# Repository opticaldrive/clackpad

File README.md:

# clackpad

This is a 2x4 macropad with neopixel underlighting! It's supposed to help make me more productive(WIP) on my computer\
Not pictured is a gesture sensor, which is present on the physical pcb(but the case doesn't have a hole for it sob) \
| Item Name | Description | Quantity | Cost |
|-----------|-------------|----------|------|
| PCB | Main Macropad PCB | 5 | ~9USD |
| Seeed Studio Xiao RP2040 | Main MCU | 1 | N/A Hackpad Provided |
| CherryMX Switches | Keyswitches, the buttons on the macropad | 8 | N/A Hackpad Provided |
| Diodes | Diodes for matrix to prevent ghosting | 8 | N/A Hackpad Provided |
| SK6812 MINI-E  | backlighting? flashing? neopixels! | 8 | N/A Hackpad Provided |

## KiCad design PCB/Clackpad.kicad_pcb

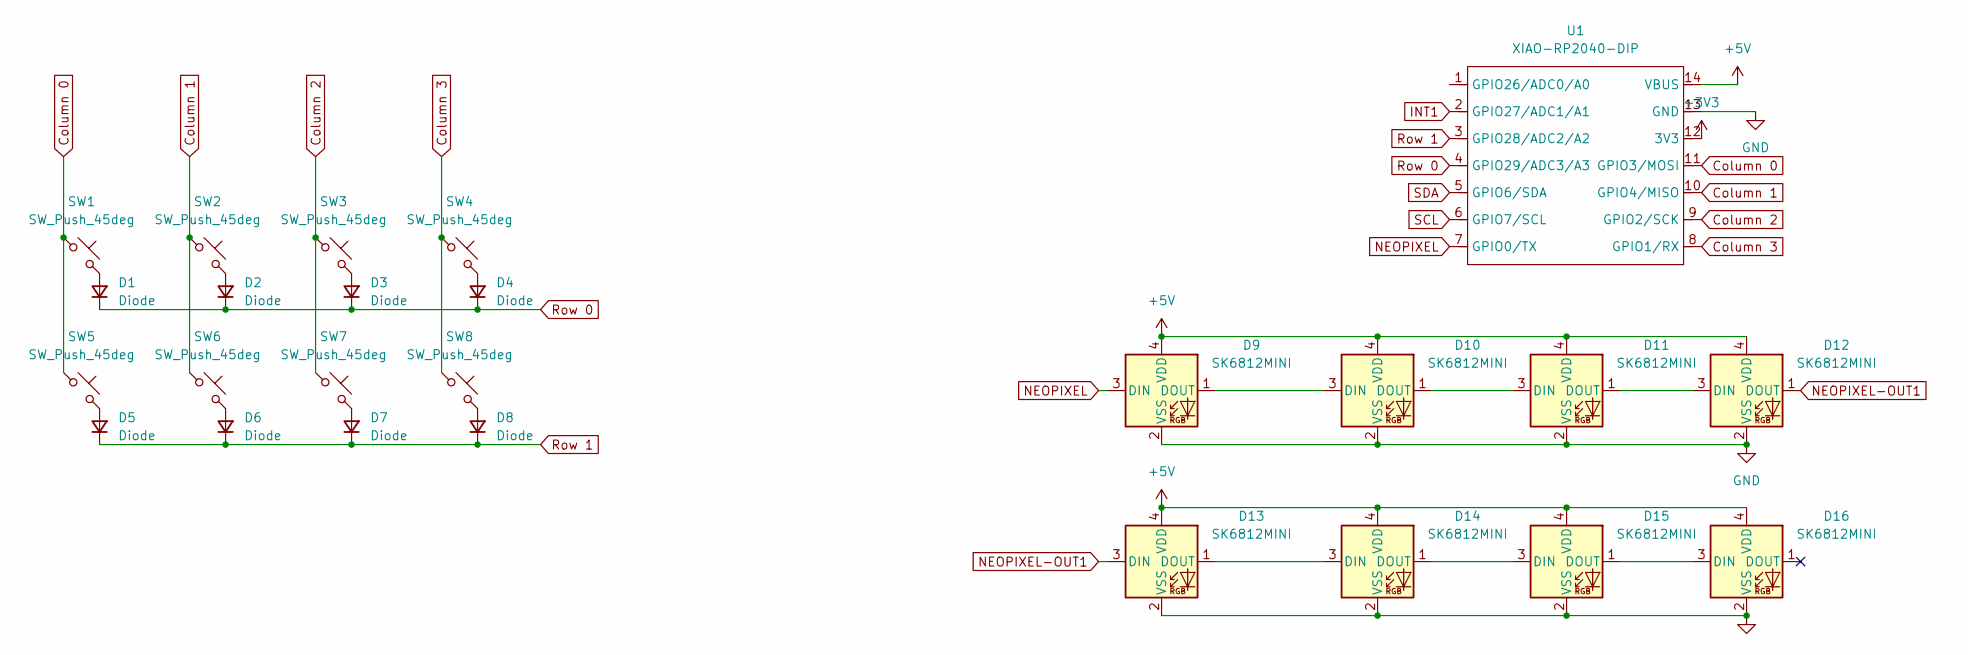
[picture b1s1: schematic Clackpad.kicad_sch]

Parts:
D1, D2, D3, D4, D5, D6, D7, D8: Diode; D_DO-35_SOD27_P7.62mm_Horizontal
D9, D10, D11, D12, D13, D14, D15, D16: SK6812MINI; SK6812-MINI-E
SW1, SW2, SW3, SW4, SW5, SW6, SW7, SW8: SW_Push_45deg; SW_Cherry_MX_1.00u_PCB
U1: XIAO-RP2040-DIP

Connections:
+3V3: U1.12 (3V3)
+5V: D9.4 (VDD), D10.4 (VDD), D11.4 (VDD), D12.4 (VDD), D13.4 (VDD), D14.4 (VDD), D15.4 (VDD), D16.4 (VDD), U1.14 (VBUS)
Column 0: SW1.1, SW5.1, U1.11 (GPIO3/MOSI)
Column 1: SW2.1, SW6.1, U1.10 (GPIO4/MISO)
Column 2: SW3.1, SW7.1, U1.9 (GPIO2/SCK)
Column 3: SW4.1, SW8.1, U1.8 (GPIO1/RX)
GND: D9.2 (VSS), D10.2 (VSS), D11.2 (VSS), D12.2 (VSS), D13.2 (VSS), D14.2 (VSS), D15.2 (VSS), D16.2 (VSS), U1.13 (GND)
INT1: U1.2 (GPIO27/ADC1/A1)
NEOPIXEL: D9.3 (DIN), U1.7 (GPIO0/TX)
NEOPIXEL-OUT1: D12.1 (DOUT), D13.3 (DIN)
unnamed: D1.2 (A), SW1.2
unnamed: D2.2 (A), SW2.2
unnamed: D3.2 (A), SW3.2
unnamed: D4.2 (A), SW4.2
unnamed: D5.2 (A), SW5.2
unnamed: D6.2 (A), SW6.2
unnamed: D7.2 (A), SW7.2
unnamed: D8.2 (A), SW8.2
unnamed: D9.1 (DOUT), D10.3 (DIN)
unnamed: D10.1 (DOUT), D11.3 (DIN)
unnamed: D11.1 (DOUT), D12.3 (DIN)
unnamed: D13.1 (DOUT), D14.3 (DIN)
unnamed: D14.1 (DOUT), D15.3 (DIN)
unnamed: D15.1 (DOUT), D16.3 (DIN)
Row 0: D1.1 (K), D2.1 (K), D3.1 (K), D4.1 (K), U1.4 (GPIO29/ADC3/A3)
Row 1: D5.1 (K), D6.1 (K), D7.1 (K), D8.1 (K), U1.3 (GPIO28/ADC2/A2)
SCL: U1.6 (GPIO7/SCL)
SDA: U1.5 (GPIO6/SDA)

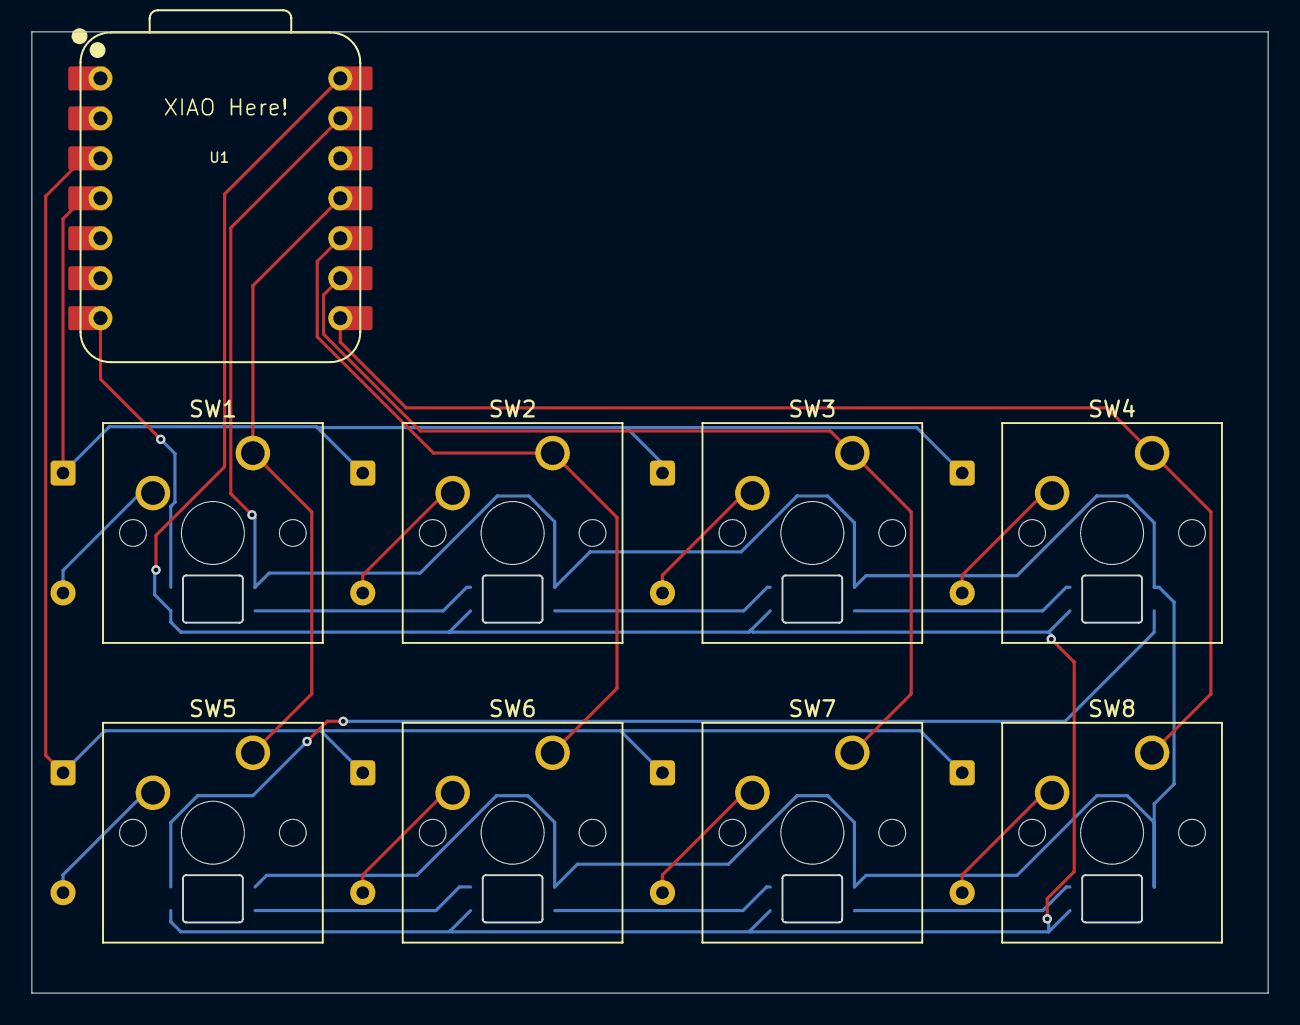
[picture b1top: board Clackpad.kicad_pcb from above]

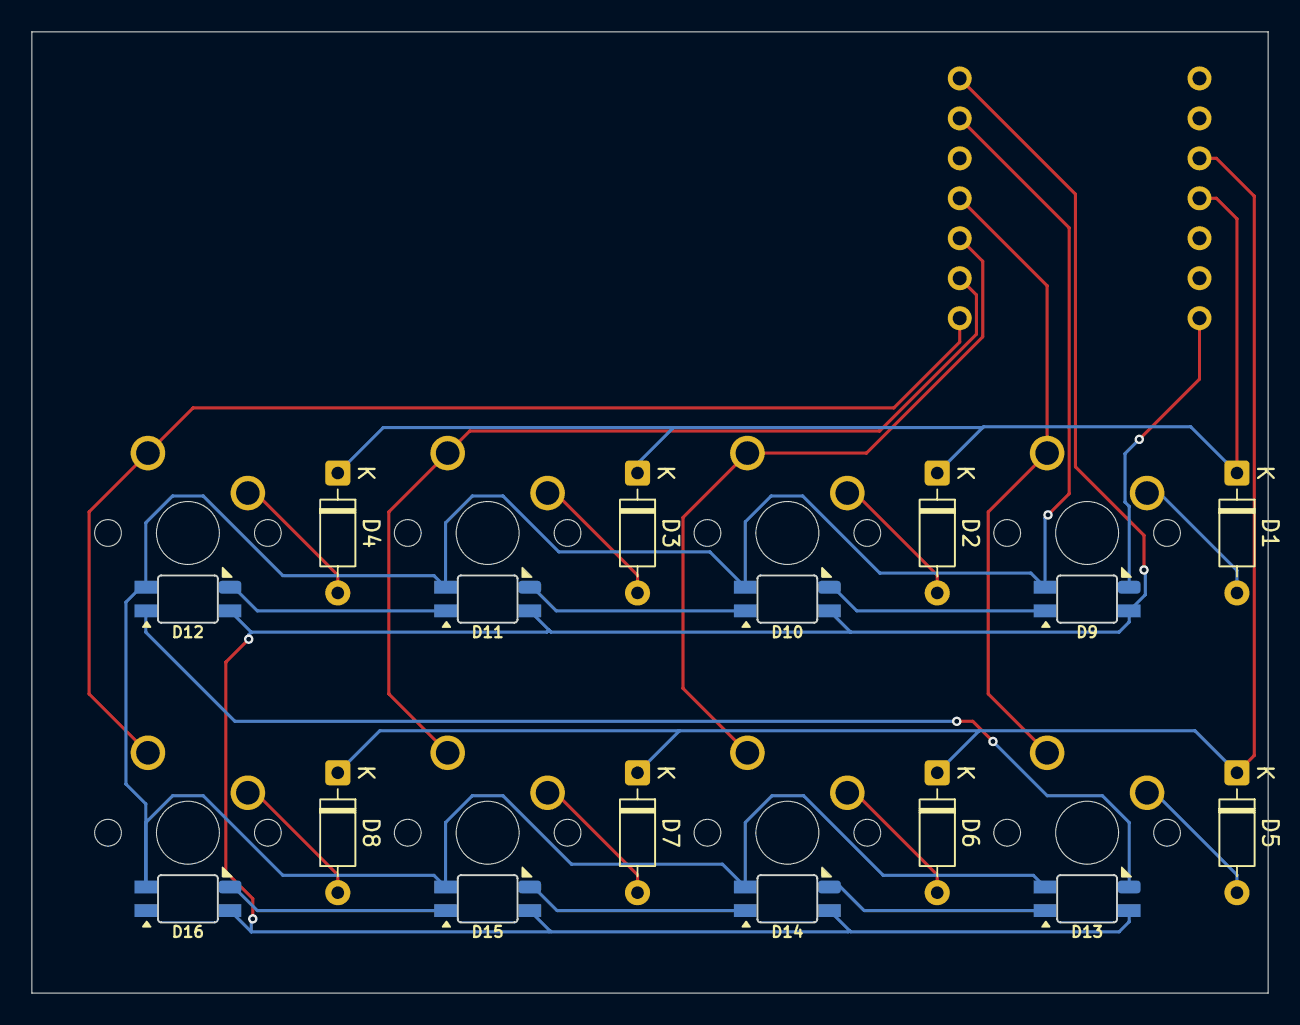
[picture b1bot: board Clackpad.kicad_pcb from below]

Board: 2 copper layers, 78.5 x 61.0 mm, 25 parts (16 on the bottom side), 24 nets.

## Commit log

2025-07-10 Adding some prod files - no firmware
2025-07-10 readme or not
2025-07-10 firmware 1
2025-07-10 duplicates yay
2025-07-10 hope this works
2025-07-10 commit go
2025-07-10 [ImgBot] Optimize images
    *Total -- 619.48kb -> 431.71kb (30.31%)
    /assets/image.png -- 320.95kb -> 189.33kb (41.01%)
    /assets/image-2.png -- 78.53kb -> 61.46kb (21.73%)
    /assets/image-1.png -- 220.00kb -> 180.92kb (17.77%)
2025-07-10 aaaa
2025-07-10 CSV hope
